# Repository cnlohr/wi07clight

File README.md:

I tried to get this all working in 5? 6? hours.  Did not happen.
It is a light that can have its intensity changed.  I will likely
link the youtube video here.

This "wi07" library is still in its infancy.  It's for use with the
ESP8266 chips.  It uses the UART on the AVR to communicate.

Charles

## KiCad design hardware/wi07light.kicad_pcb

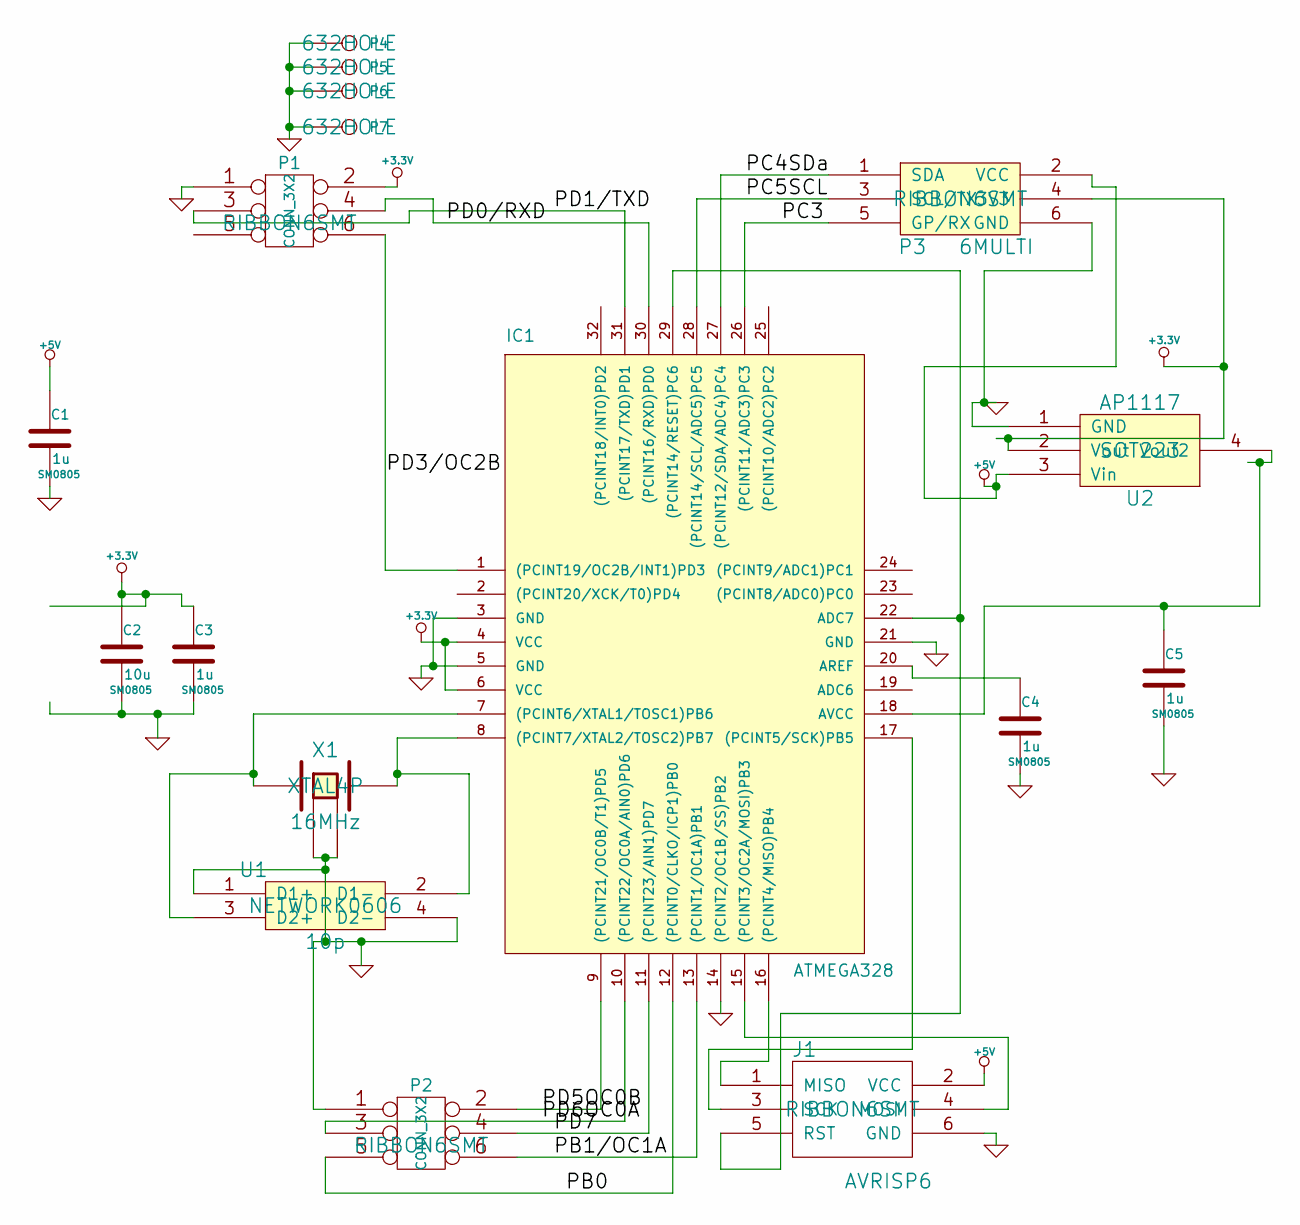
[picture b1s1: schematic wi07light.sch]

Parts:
C1, C3, C4, C5: 1u; SM0805
C2: 10u; SM0805
IC1: ATMEGA328; TQFP32
J1: AVRISP6; RIBBON6SMT
P1, P2: CONN_3X2; RIBBON6SMT
P3: 6MULTI; RIBBON6SMT
P4, P5, P6, P7: CONN_1; 632HOLE
U1: 10p; NETWORK0606
U2: AP1117; SOT223
X1: 16MHz; XTAL4P

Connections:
+3.3V: C2.1, C3.1, IC1.4 (VCC), IC1.6 (VCC), P1.2, P3.4 (3V3), U2.2 (Vout)
+5V: C1.1, J1.2 (VCC), P3.2 (VCC), U2.3 (Vin)
/PB0: IC1.12 ((PCINT0/CLKO/ICP1)PB0), P2.5
/PB1/OC1A: IC1.13 ((PCINT1/OC1A)PB1), P2.6
/PC3: IC1.26 ((PCINT11/ADC3)PC3), P3.5 (GP/RX)
/PC4SDa: IC1.27 ((PCINT12/SDA/ADC4)PC4), P3.1 (SDA)
/PC5SCL: IC1.28 ((PCINT14/SCL/ADC5)PC5), P3.3 (SCL/TX)
/PD0/RXD: IC1.30 ((PCINT16/RXD)PD0), P1.4
/PD1/TXD: IC1.31 ((PCINT17/TXD)PD1), P1.3
/PD3/OC2B: IC1.1 ((PCINT19/OC2B/INT1)PD3), P1.6
/PD5OC0B: IC1.9 ((PCINT21/OC0B/T1)PD5), P2.2
/PD6OC0A: IC1.10 ((PCINT22/OC0A/AIN0)PD6), P2.3
/PD7: IC1.11 ((PCINT23/AIN1)PD7), P2.4
GND: C1.2, C2.2, C3.2, C4.2, C5.2, IC1.3 (GND), IC1.5 (GND), IC1.14 ((PCINT2/OC1B/SS)PB2), IC1.21 (GND), J1.6 (GND), P1.1, P2.1, P3.6 (GND), P4.1, P5.1, P6.1, P7.1, U1.1 (D1+), U1.4 (D2-), U2.1 (GND), X1.3 (GND), X1.4 (GND)
unnamed: IC1.7 ((PCINT6/XTAL1/TOSC1)PB6), U1.3 (D2+), X1.1
unnamed: IC1.8 ((PCINT7/XTAL2/TOSC2)PB7), U1.2 (D1-), X1.2
unnamed: IC1.22 (ADC7), IC1.29 ((PCINT14/RESET)PC6), J1.5 (RST)
unnamed: C4.1, IC1.20 (AREF)
unnamed: C5.1, IC1.18 (AVCC), U2.4 (Vout2)
unnamed: IC1.16 ((PCINT4/MISO)PB4), J1.1 (MISO)
unnamed: IC1.17 ((PCINT5/SCK)PB5), J1.3 (SCK)
unnamed: IC1.15 ((PCINT3/OC2A/MOSI)PB3), J1.4 (MOSI)

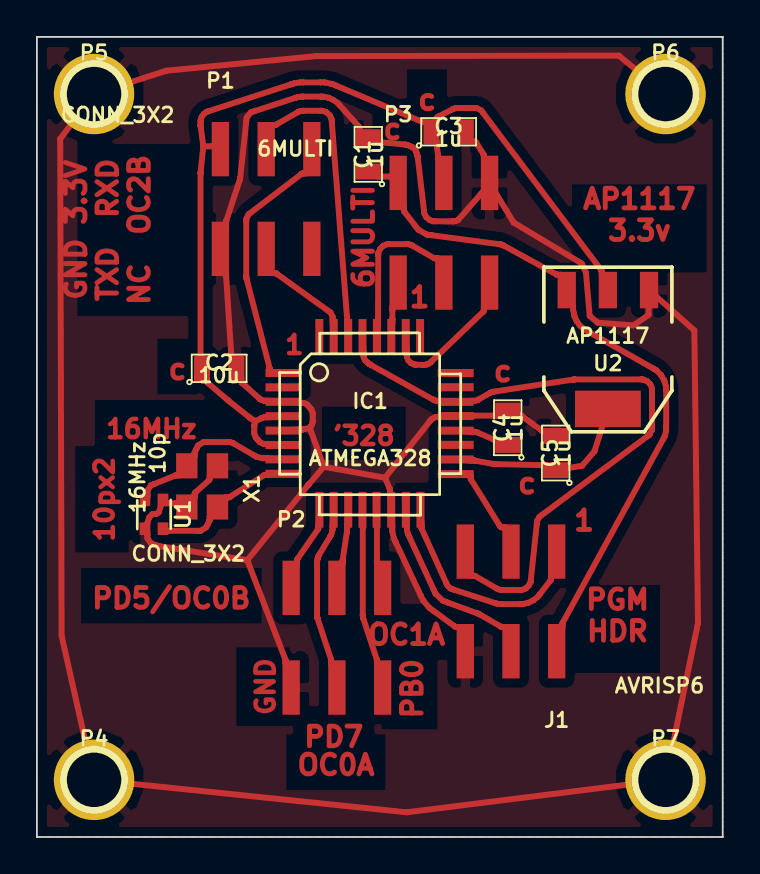
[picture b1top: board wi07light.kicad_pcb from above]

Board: 2 copper layers, 38.1 x 44.5 mm, 17 parts (0 on the bottom side), 22 nets.

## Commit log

2014-09-14 add a bunch of stuff
2014-09-14 update the readme
2014-11-29 update ap's
